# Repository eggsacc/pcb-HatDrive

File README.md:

# BLDC Hat

A four-layer BLDC motor driver hat built around the TI DRV8316C for the [STM32F405 development module](https://github.com/eggsacc/stm32f405-module). It is intended for six-PWM motor control and field-oriented control experiments.

## Hardware

- Three-phase driver with six PWM inputs, three low-side current-sense outputs, SPI configuration/status, and motor-supply voltage sensing.
- Onboard 5 V buck converter with a switch for MCU power, plus power and fault LEDs.
- Four-layer PCB; board revision V1.4.

## Connectors

| Connector | Purpose |
| --- | --- |
| CN1 · XT30 | Motor power input (`VM_IN`) |
| U3 · MR30 | Three motor phases (`U`, `V`, `W`) |
| J2 · 2×10 | Interface to the STM32F405 module |
| J4 · 2×3 | Six PWM inputs (`CH1–3`, `C1N–3N`) |
| J1 · 2×3 | Driver SPI (`CLK`, `CS`, `MI`, `SI`, 3V3, GND) |
| J5 · 1×4 | I²C (`SDA`, `SCL`, 3V3, GND) |
| CN2 · XT30 | Optional motor-power output; marked DNP in the BOM |

With `MCU PWR` on, the hat supplies 5 V to the MCU module. Its [power guidance](https://github.com/eggsacc/stm32f405-module#power) warns against connecting USB and external 5 V at the same time.

## Layout
>L1: Power & signal

>L2: GND

>L3: GND + PWM signal

>L4: GND + signal

> Silkscreen

>Combined

The [KiCad project](HatDrive_kicad/) contains the schematic, PCB, and manufacturing files. See the [MCU module README](https://github.com/eggsacc/stm32f405-module) for its pinout.

---

<div align="center">
Designed by <b>@eggsacc</b> · HatDrive V1.4 <br>
Updated 02/10/2026
</div>

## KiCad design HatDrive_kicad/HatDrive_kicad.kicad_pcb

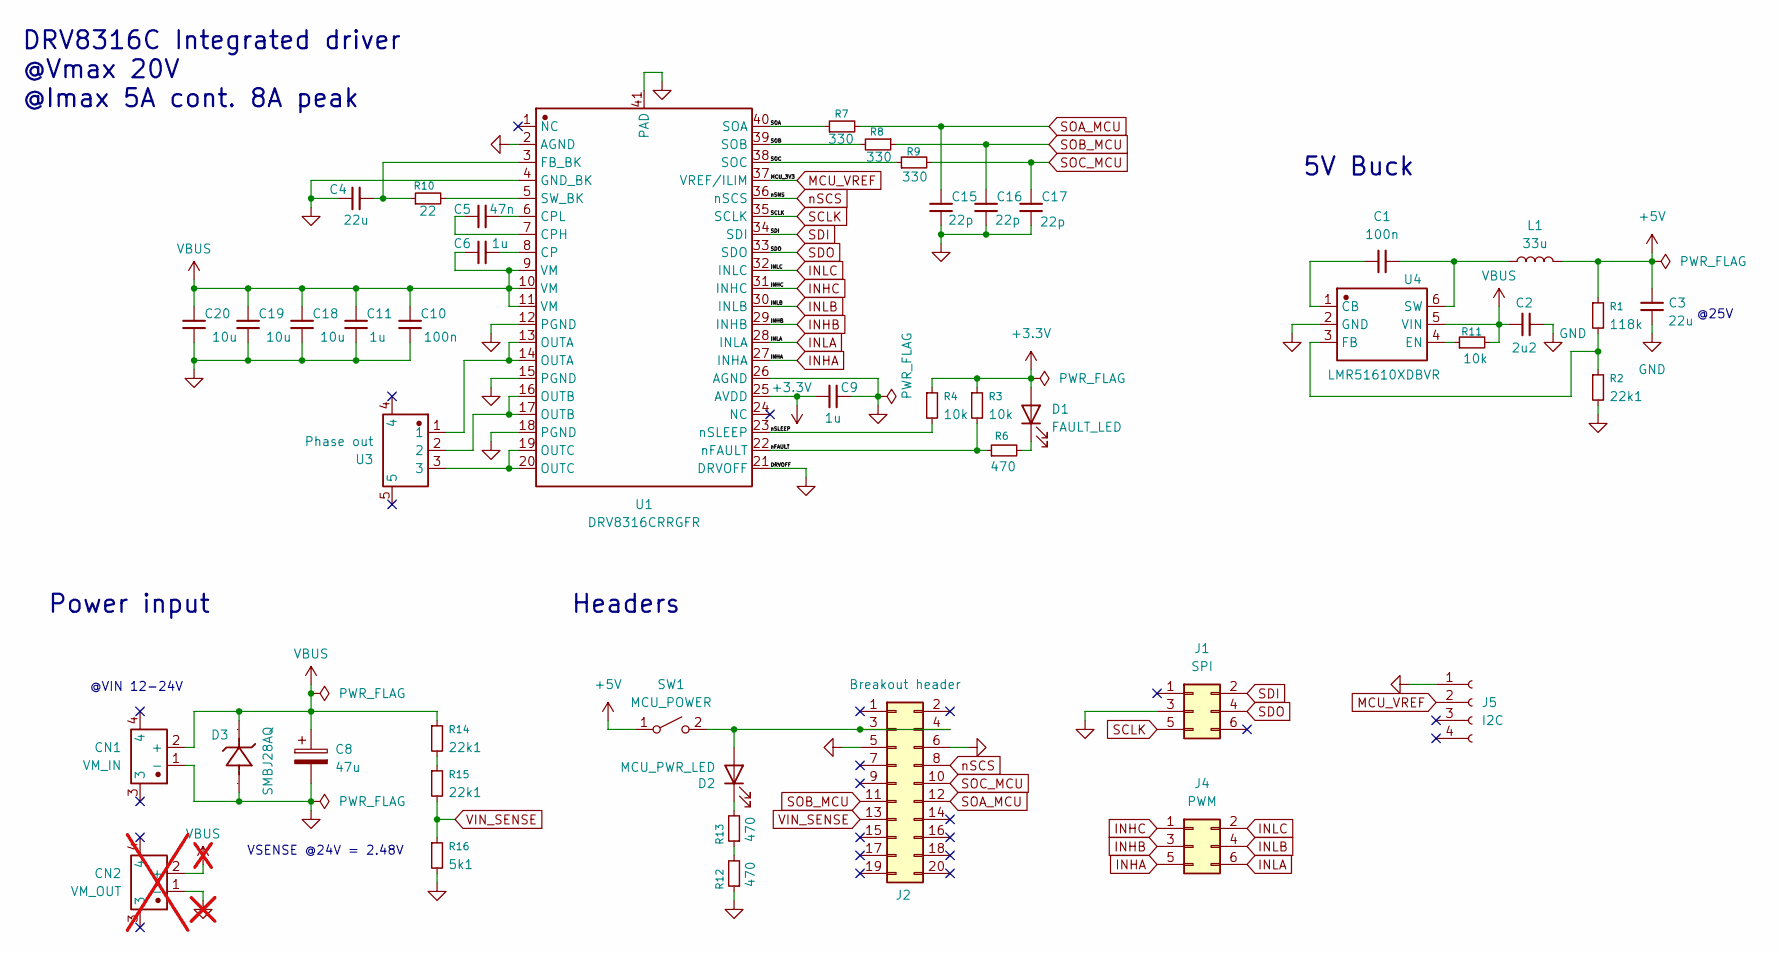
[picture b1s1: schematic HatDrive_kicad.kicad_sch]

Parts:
C1, C10: 100n; C_0402_1005Metric
C2: 2u2; C_1206_3216Metric
C3: 22u; C_1210_3225Metric
C4: 22u; C_0805_2012Metric
C5: 47n; C_0603_1608Metric
C6, C11: 1u; C_0603_1608Metric
C8: 47u; CP_Elec_6.3x7.7
C9: 1u; C_0402_1005Metric
C15, C16, C17: 22p; C_0402_1005Metric
C18, C19, C20: 10u; C_1210_3225Metric
CN1: VM_IN; CONN-TH_XT30PW-M; Manufacturer Part XT30PW-M
CN2: VM_OUT; CONN-TH_XT30PW-M; Manufacturer Part XT30PW-M; not fitted
D1: FAULT_LED; LED_0402_1005Metric
D2: MCU_PWR_LED; LED_0402_1005Metric
D3: SMBJ28AQ; SMB_L4.3-W3.6-LS5.3-RD; Manufacturer Part SMBJ28AQ
J1: SPI; PinHeader_2x03_P2.54mm_Vertical
J2: Breakout header; PinHeader_2x10_P2.54mm_Vertical
J4: PWM; PinHeader_2x03_P2.54mm_Vertical
J5: I2C; PinHeader_1x04_P2.54mm_Vertical
L1: 33u; L_6.3x6.3_H3
R1: 118k; R_0402_1005Metric
R2, R14, R15: 22k1; R_0402_1005Metric
R3, R4, R11: 10k; R_0402_1005Metric
R6, R12, R13: 470; R_0402_1005Metric
R7, R8, R9: 330; R_0402_1005Metric
R10: 22; R_0402_1005Metric
R16: 5k1; R_0402_1005Metric
SW1: MCU_POWER; SW_DIP_SPSTx01_Slide_6.7x4.1mm_W6.73mm_P2.54mm_LowProfile_J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
U1: DRV8316CRRGFR; DRV8316CR; Manufacturer Part DRV8316CRRGFR
U3: Phase out; CONN-TH_MR30PW-M30-G-Y; Manufacturer Part MR30PW-M30.G.Y
U4: LMR51610XDBVR; SOT-23-6; Manufacturer Part LMR51610XDBVR

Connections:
+3.3V: C9.1, D1.2 (A), R3.1, R4.1, U1.25 (AVDD)
/SOA: R7.1, U1.40 (SOA)
/SOB: R8.2, U1.39 (SOB)
/SOC: R9.1, U1.38 (SOC)
/nFAULT: R3.2, R6.1, U1.22 (nFAULT)
/nSLEEP: R4.2, U1.23 (nSLEEP)
GND: C2.1, C3.2, C4.2, C8.2, C9.2, C10.2, C11.2, C15.2, C16.2, C17.2, C18.2, C19.2, C20.2, CN1.1 (-), CN2.1 (-), D3.2 (A), J1.3, J2.5, J2.6, J5.1, R2.2, R12.1, R16.2, U1.2 (AGND), U1.4 (GND_BK), U1.12 (PGND), U1.15 (PGND), U1.18 (PGND), U1.21 (DRVOFF), U1.26 (AGND), U1.41 (PAD), U4.2 (GND)
INHA: J4.5, U1.27 (INHA)
INHB: J4.3, U1.29 (INHB)
INHC: J4.1, U1.31 (INHC)
INLA: J4.6, U1.28 (INLA)
INLB: J4.4, U1.30 (INLB)
INLC: J4.2, U1.32 (INLC)
MCU_VREF: J5.2, U1.37 (VREF/ILIM)
unnamed: D1.1 (K), R6.2
unnamed: D2.1 (K), R13.2
unnamed: R12.2, R13.1
unnamed: R14.2, R15.1
unnamed: C6.2, U1.8 (CP)
unnamed: C5.1, U1.7 (CPH)
unnamed: C5.2, U1.6 (CPL)
unnamed: C4.1, R10.1, U1.3 (FB_BK)
unnamed: U1.13 (OUTA), U1.14 (OUTA), U3.1
unnamed: U1.16 (OUTB), U1.17 (OUTB), U3.2
unnamed: U1.19 (OUTC), U1.20 (OUTC), U3.3
unnamed: R10.2, U1.5 (SW_BK)
unnamed: C1.1, U4.1 (CB)
unnamed: R11.1, U4.4 (EN)
unnamed: R1.2, R2.1, U4.3 (FB)
unnamed: C1.2, L1.1, U4.6 (SW)
SCLK: J1.5, U1.35 (SCLK)
SDI: J1.2, U1.34 (SDI)
SDO: J1.4, U1.33 (SDO)
SOA_MCU: C15.1, J2.12, R7.2
SOB_MCU: C16.1, J2.11, R8.1
SOC_MCU: C17.1, J2.10, R9.2
VBUS: C2.2, C6.1, C8.1, C10.1, C11.1, C18.1, C19.1, C20.1, CN1.2 (+), CN2.2 (+), D3.1 (C), R11.2, R14.1, U1.9 (VM), U1.10 (VM), U1.11 (VM), U4.5 (VIN)
VIN_SENSE: J2.13, R15.2, R16.1
nSCS: J2.8, U1.36 (nSCS)

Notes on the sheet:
DRV8316C Integrated driver @Vmax 20V @Imax 5A cont. 8A peak
VSENSE @24V = 2.48V
Power input
5V Buck
@VIN 12-24V
Headers
@25V

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
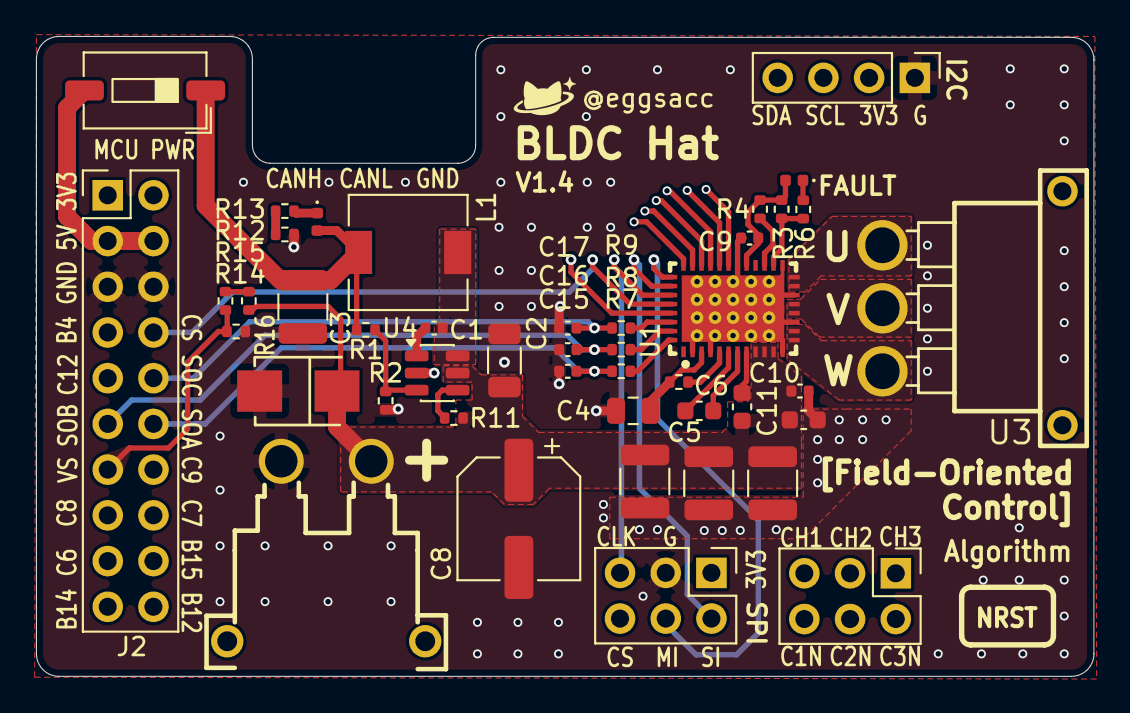
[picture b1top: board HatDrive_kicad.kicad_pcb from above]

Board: 4 copper layers, 58.8 x 35.5 mm, 44 parts (0 on the bottom side), 41 nets.
